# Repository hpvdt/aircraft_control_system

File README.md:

# Aircraft Control System

Used for the yet unnamed aircraft project

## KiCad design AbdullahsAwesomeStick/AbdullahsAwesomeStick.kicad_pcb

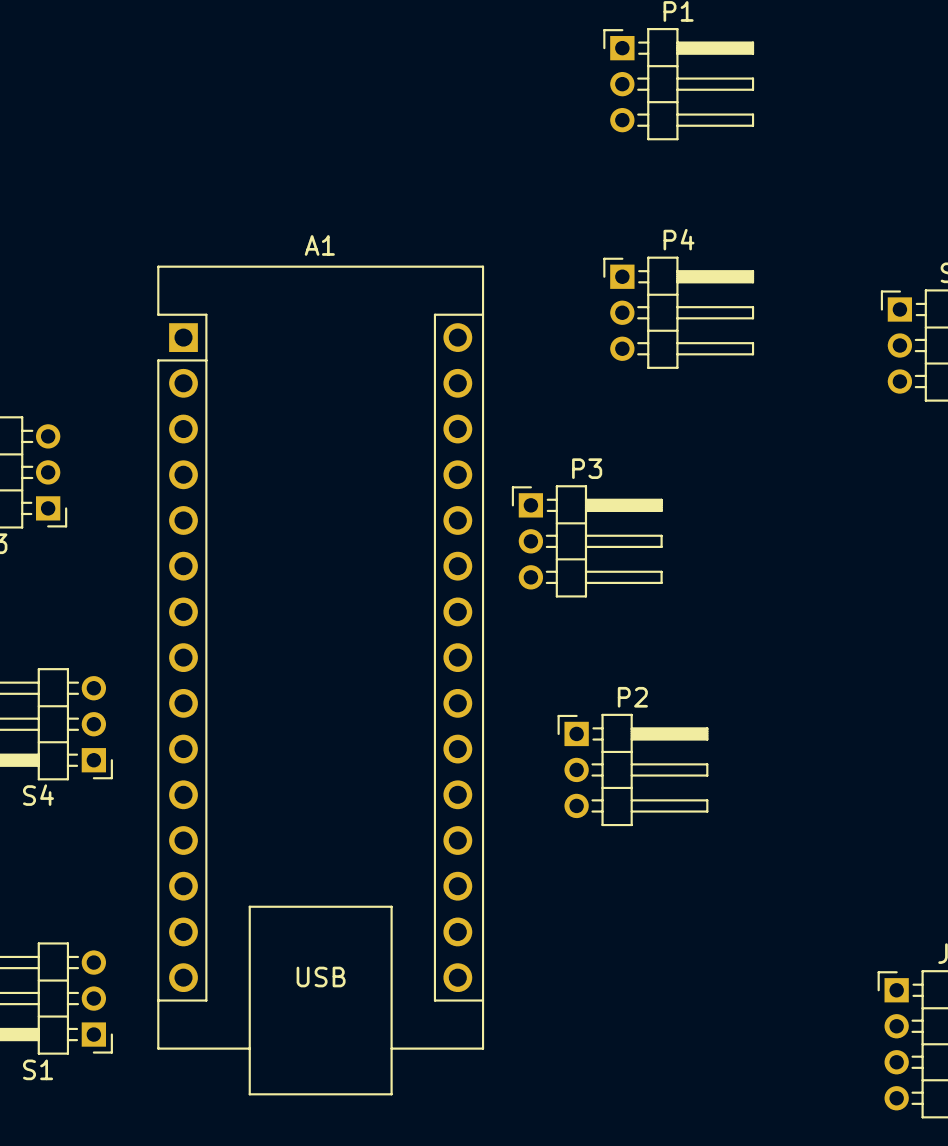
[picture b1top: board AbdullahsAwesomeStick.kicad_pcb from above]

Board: 2 copper layers, 10 parts (0 on the bottom side), 10 nets, no tracks yet.

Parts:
A1: Arduino_Nano_v2.x; Arduino_Nano
J5: Conn_01x04_Socket; PinHeader_1x04_P2.00mm_Horizontal
P1, P2, P3, P4: Conn_01x03_Pin; PinHeader_1x03_P2.00mm_Horizontal
S1, S2, S3, S4: Conn_01x03_Pin; PinHeader_1x03_P2.00mm_Horizontal

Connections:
+5V: J5.1, P1.1, P2.1, P3.1, P4.1, S1.1, S2.1, S3.1, S4.1
GND: J5.4, P1.3, P2.3, P3.3, P4.3, S1.3, S2.3, S3.3, S4.3
unnamed: A1.19 (A0), S1.2
unnamed: A1.20 (A1), S2.2
unnamed: A1.21 (A2), S3.2
unnamed: A1.22 (A3), S4.2
unnamed: A1.23 (A4), P1.2
unnamed: A1.24 (A5), P2.2
unnamed: A1.25 (A6), P3.2
unnamed: A1.26 (A7), P4.2

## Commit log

2022-11-26 Upload of initial aircraft control code
2023-01-22 Added prelimary flightstick code
    Code was from Abdullah with the resistance function written by me
2023-01-25 normalized resistance [-1,1]
2023-01-25 no more introductory code
2023-02-08 Create AWESOMEINPUT2(servomovement)
2023-02-22 String Data, 3 Values
2023-02-22 Extra Potentiometer, Float to String, 3 Values
2023-02-25 Create joystickreadingupdated
2023-02-25 Create JoystickReading4ServoWIP
2023-02-25 Update JoystickReading4ServoWIP
2023-03-18 kicad files for pcb
2023-03-18 deletd these backusp
2023-03-18 wip voltage regulator RT6215EHGJ8F kicad files
2023-03-21 updated with new one
2023-03-21 added updated files of kicad schematic
    voltage regulator, finsihed version of schematic if savo says its ok :)
